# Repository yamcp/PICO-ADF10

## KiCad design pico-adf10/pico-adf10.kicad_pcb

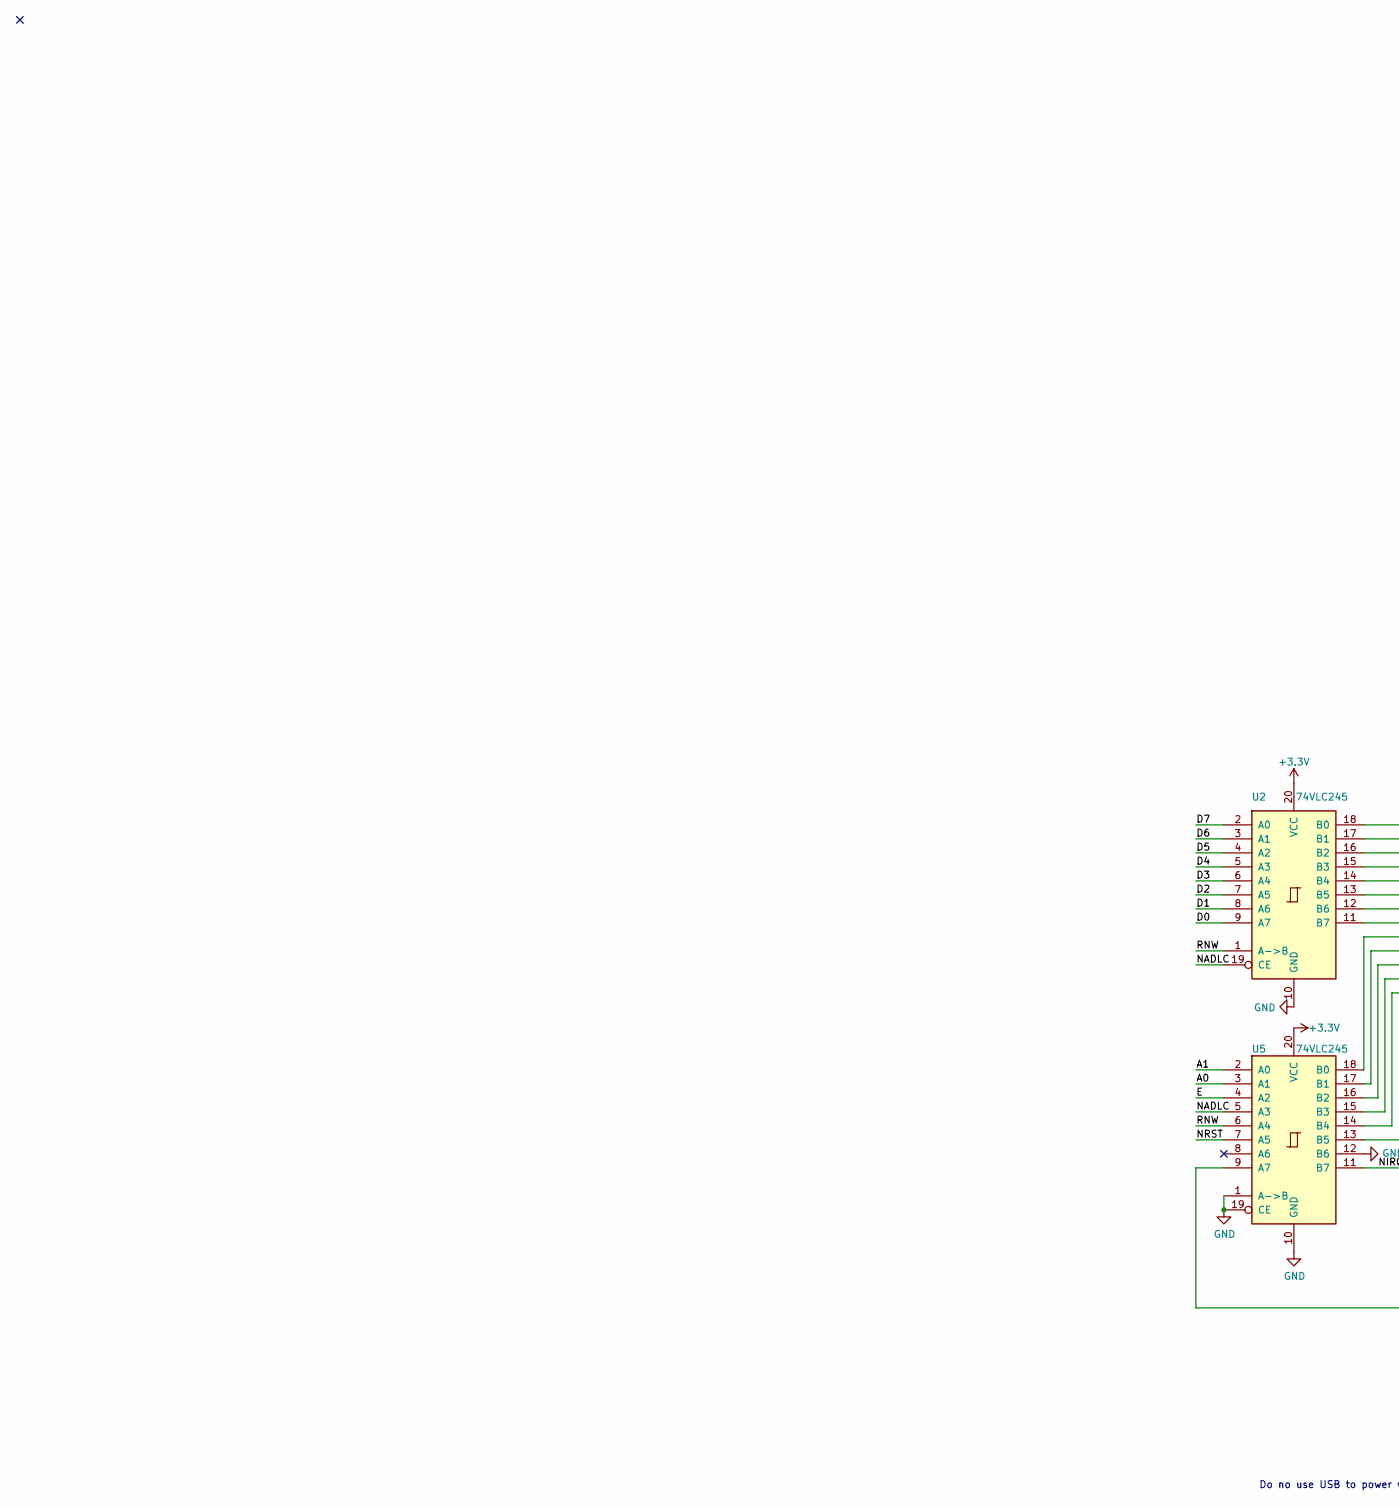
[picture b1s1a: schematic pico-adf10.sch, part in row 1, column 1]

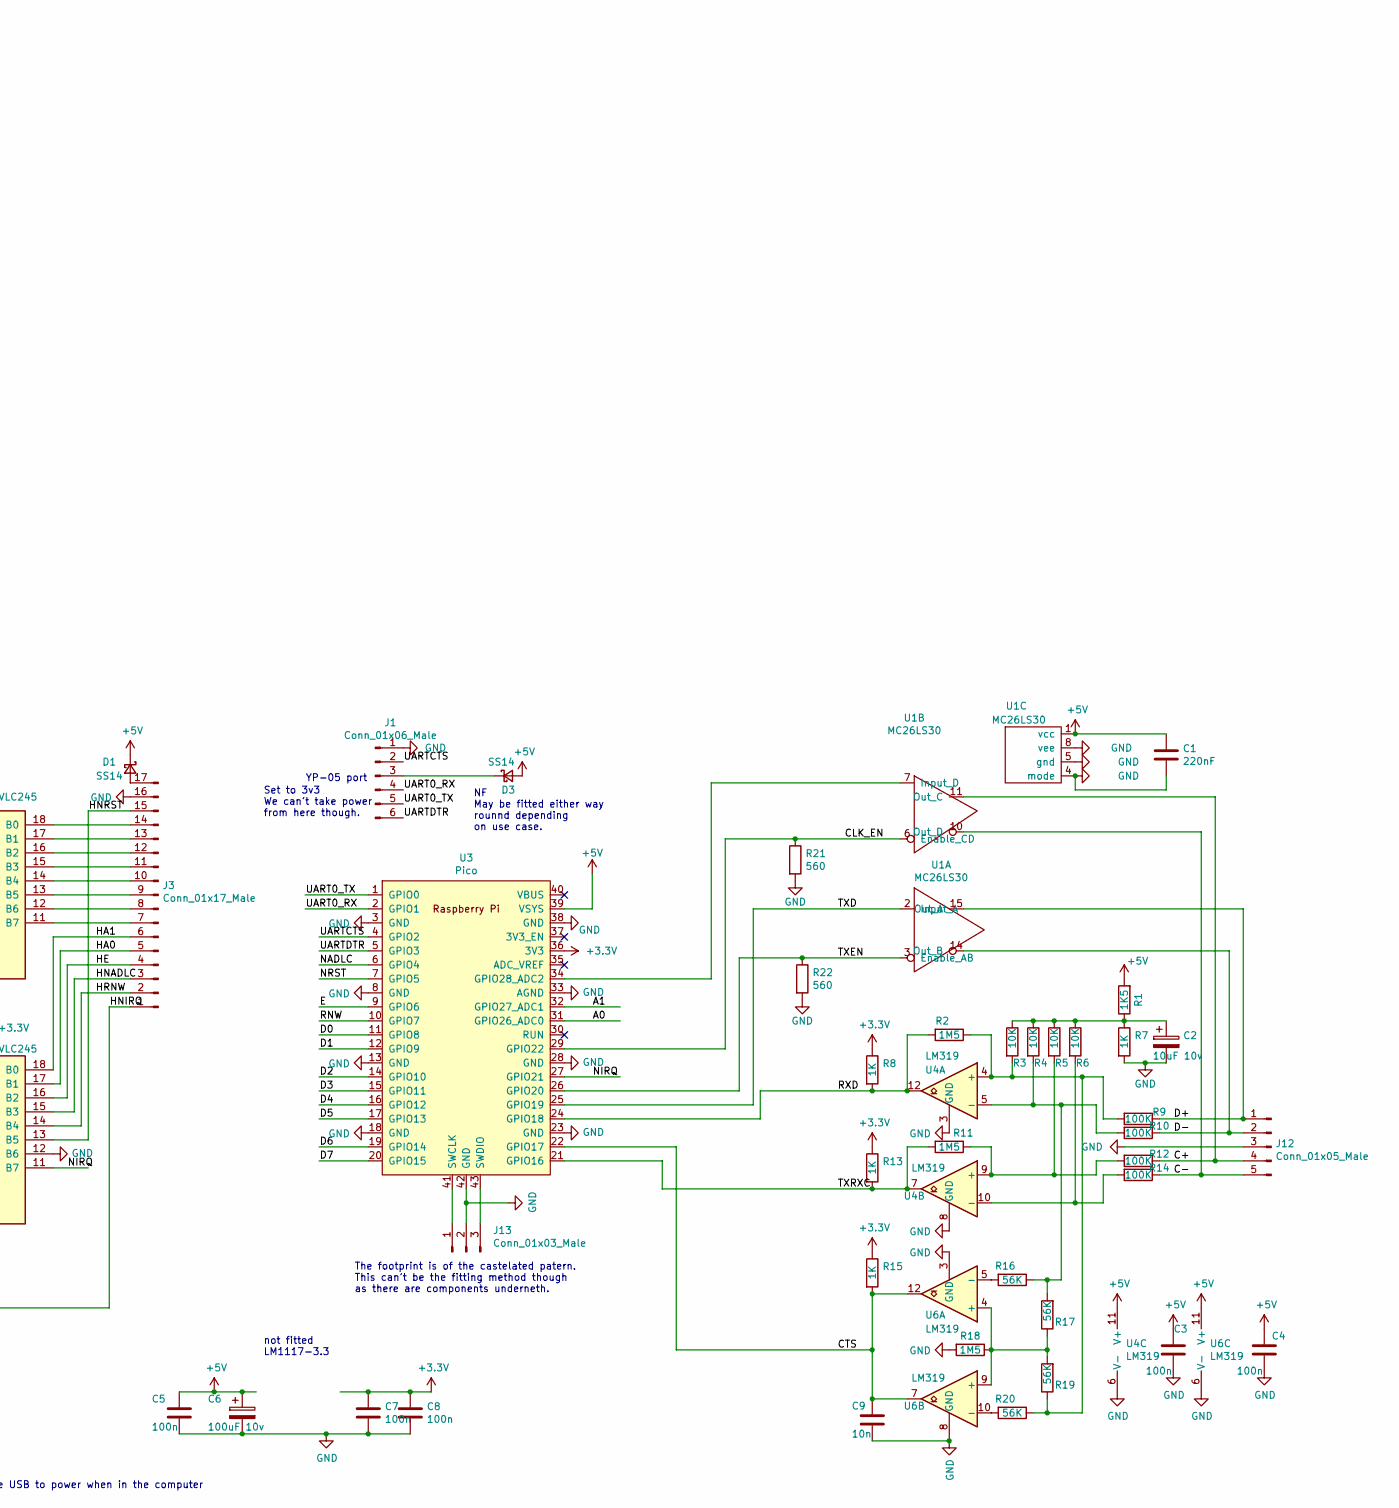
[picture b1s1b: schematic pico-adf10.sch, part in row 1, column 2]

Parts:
C1: 220nF; C_0805_2012Metric_Pad1.18x1.45mm_HandSolder
C2: 10uF 10v; C_0805_2012Metric_Pad1.18x1.45mm_HandSolder
C3, C4, C5, C7, C8: 100n; C_0805_2012Metric_Pad1.18x1.45mm_HandSolder
C6: 100uF 10v; CP_Elec_8x6.2
C9: 10n; C_0805_2012Metric_Pad1.18x1.45mm_HandSolder
D1, D3: SS14; D_SMA
J1: Conn_01x06_Male; PinHeader_1x06_P2.54mm_Vertical
J3: Conn_01x17_Male; PinHeader_1x17_P2.54mm_Vertical
J12: Conn_01x05_Male; PinHeader_1x05_P2.54mm_Vertical
J13: Conn_01x03_Male; PinHeader_1x03_P2.54mm_Vertical
R1: 1K5; R_0805_2012Metric_Pad1.20x1.40mm_HandSolder
R2, R11, R18: 1M5; R_0805_2012Metric_Pad1.20x1.40mm_HandSolder
R3, R4, R5, R6: 10K; R_0805_2012Metric_Pad1.20x1.40mm_HandSolder
R7, R8, R13, R15: 1K; R_0805_2012Metric_Pad1.20x1.40mm_HandSolder
R9, R10, R12, R14: 100K; R_0805_2012Metric_Pad1.20x1.40mm_HandSolder
R16, R17, R19, R20: 56K; R_0805_2012Metric_Pad1.20x1.40mm_HandSolder
R21, R22: 560; R_0805_2012Metric_Pad1.20x1.40mm_HandSolder
U1: MC26LS30; DIP-16_W7.62mm
U2, U5: 74VLC245; SOP-20_7.5x12.8mm_P1.27mm
U3: Pico; RPi_Pico_SMD_TH
U4, U6: LM319; SO-14_3.9x8.65mm_P1.27mm

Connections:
+3V3: C7.1, C8.1, R8.1, R13.1, R15.1, U2.20 (VCC), U3.36 (3V3), U5.20 (VCC)
+5V: C1.1, C3.1, C4.1, C5.1, C6.1, D1.1 (K), D3.2 (A), R1.2, U1.1 (vcc), U3.39 (VSYS), U4.11 (V+), U6.11 (V+)
/A0: U3.31 (GPIO26_ADC0), U5.3 (A1)
/A1: U3.32 (GPIO27_ADC1), U5.2 (A0)
/C+: J12.4, R12.1, U1.11 (Out_C)
/C-: J12.5, R14.1, U1.10 (Out_D)
/CLK_EN: R21.1, U1.6 (Enable_CD), U3.29 (GPIO22)
/CTS: C9.1, R15.2, U3.22 (GPIO17), U6.7, U6.12
/D0: U2.9 (A7), U3.11 (GPIO8)
/D1: U2.8 (A6), U3.12 (GPIO9)
/D2: U2.7 (A5), U3.14 (GPIO10)
/D3: U2.6 (A4), U3.15 (GPIO11)
/D4: U2.5 (A3), U3.16 (GPIO12)
/D5: U2.4 (A2), U3.17 (GPIO13)
/D6: U2.3 (A1), U3.19 (GPIO14)
/D7: U2.2 (A0), U3.20 (GPIO15)
/D+: J12.1, R9.1, U1.15 (Out_A)
/D-: J12.2, R10.1, U1.14 (Out_B)
/E: U3.9 (GPIO6), U5.4 (A2)
/HA0: J3.5, U5.17 (B1)
/HA1: J3.6, U5.18 (B0)
/HE: J3.4, U5.16 (B2)
/HNADLC: J3.3, U5.15 (B3)
/HNIRQ: J3.1, U5.9 (A7)
/HNRST: J3.15, U5.13 (B5)
/HRNW: J3.2, U5.14 (B4)
/NADLC: U2.19 (CE), U3.6 (GPIO4), U5.5 (A3)
/NIRQ: U3.27 (GPIO21), U5.11 (B7)
/NRST: U3.7 (GPIO5), U5.7 (A5)
/RNW: U2.1 (A->B), U3.10 (GPIO7), U5.6 (A4)
/RXD: R2.2, R8.2, U3.24 (GPIO18), U4.12
/TXD: U1.2 (Input_A), U3.25 (GPIO19)
/TXEN: R22.1, U1.3 (Enable_AB), U3.26 (GPIO20)
/TXRXC: R11.2, R13.2, U3.21 (GPIO16), U4.7
/UART0_RX: J1.4, U3.2 (GPIO1)
/UART0_TX: J1.5, U3.1 (GPIO0)
/UARTCTS: J1.2, U3.4 (GPIO2)
/UARTDTR: J1.6, U3.5 (GPIO3)
GND: C1.2, C2.2, C3.2, C4.2, C5.2, C6.2, C7.2, C8.2, C9.2, J1.1, J3.16, J12.3, J13.2, R7.2, R18.2, R21.2, R22.2, U1.4 (mode), U1.5 (gnd), U1.8 (vee), U2.10 (GND), U3.3 (GND), U3.8 (GND), U3.13 (GND), U3.18 (GND), U3.23 (GND), U3.28 (GND), U3.33 (AGND), U3.38 (GND), U3.42 (GND), U4.3 (GND), U4.6 (V-), U4.8 (GND), U5.1 (A->B), U5.10 (GND), U5.12 (B6), U5.19 (CE), U6.3 (GND), U6.6 (V-), U6.8 (GND)
unnamed: C2.1, R1.1, R3.1, R4.1, R5.1, R6.1, R7.1
unnamed: D1.2 (A), J3.17
unnamed: D3.1 (K), J1.3
unnamed: J3.7, U2.11 (B7)
unnamed: J3.8, U2.12 (B6)
unnamed: J3.9, U2.13 (B5)
unnamed: J3.10, U2.14 (B4)
unnamed: J3.11, U2.15 (B3)
unnamed: J3.12, U2.16 (B2)
unnamed: J3.13, U2.17 (B1)
unnamed: J3.14, U2.18 (B0)
unnamed: J13.1, U3.41 (SWCLK)
unnamed: J13.3, U3.43 (SWDIO)
unnamed: R4.2, R10.2, R16.1, R17.2, U4.5 (-)
unnamed: R5.2, R11.1, R12.2, U4.9 (+)
unnamed: R6.2, R14.2, U4.10 (-)
unnamed: R16.2, U6.5 (-)
unnamed: R17.1, R18.1, R19.2, U6.4 (+), U6.9 (+)
unnamed: R2.1, R3.2, R9.2, R19.1, R20.1, U4.4 (+)
unnamed: R20.2, U6.10 (-)
unnamed: U1.7 (Input_D), U3.34 (GPIO28_ADC2)

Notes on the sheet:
not fitted LM1117-3.3
YP-05 port
The footprint is of the castelated patern. This can't be the fitting method though as there are components underneth.
Do no use USB to power when in the computer
Set to 3v3 We can't take power from here though.
NF May be fitted either way rounnd depending on use case.

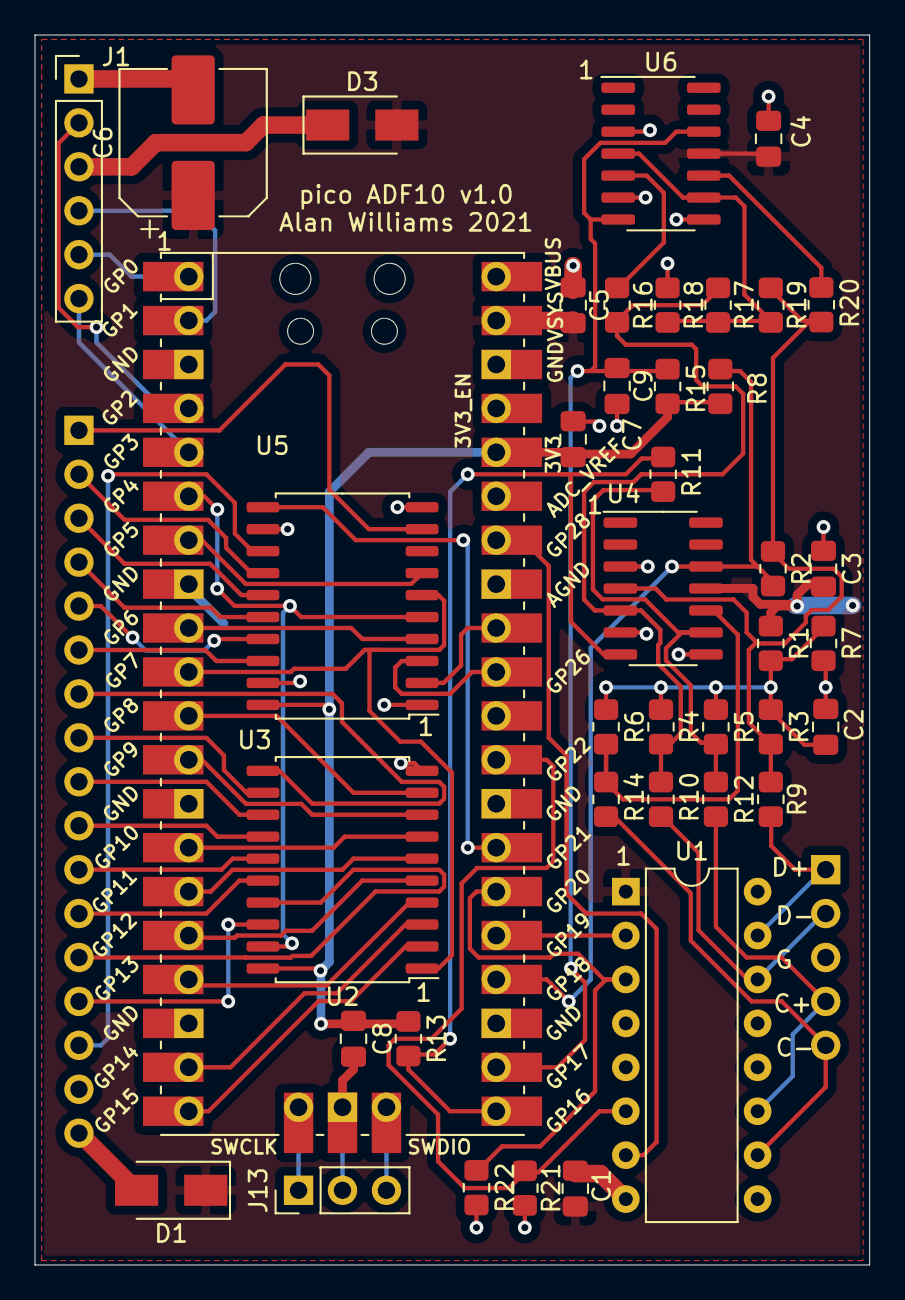
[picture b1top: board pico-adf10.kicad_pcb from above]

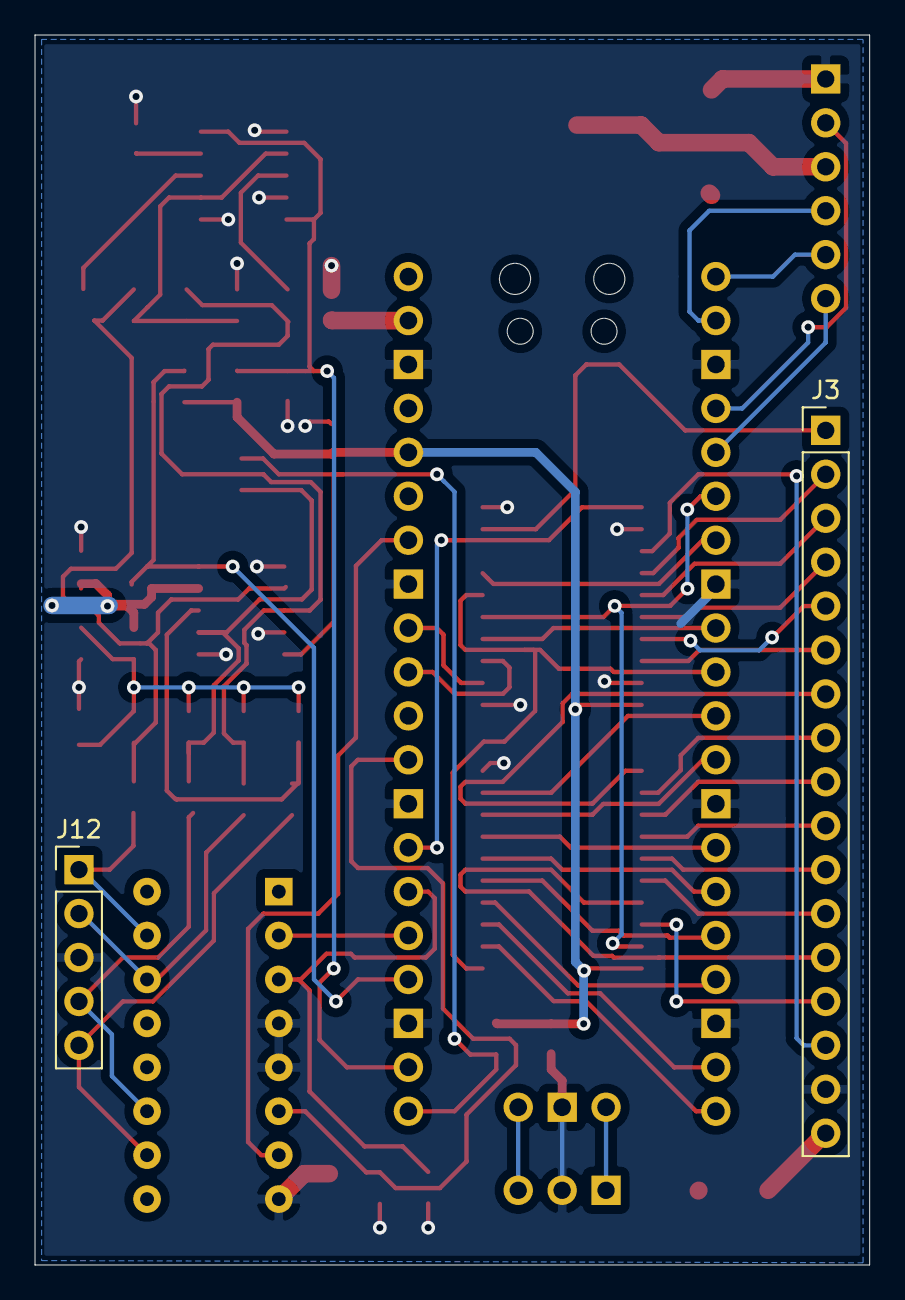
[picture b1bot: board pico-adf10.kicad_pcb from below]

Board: 2 copper layers, 48.3 x 71.1 mm, 43 parts (2 on the bottom side), 60 nets.
